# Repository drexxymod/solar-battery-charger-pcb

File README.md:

Solar Battery Charger PCB Design

This project demonstrates the design of a simple solar battery charging circuit using KiCad PCB design software.

Overview

# Solar Battery Charger PCB

## Circuit Schematic

## PCB Layout

## 3D PCB View

The circuit allows energy from a solar panel to charge a rechargeable battery while preventing reverse current flow using a protection diode.

Components

- Solar input connector
- Protection diode
- Filtering capacitor
- Battery output connector

Design Workflow

1. Circuit schematic design
2. Footprint assignment
3. PCB layout and routing
4. Board outline creation
5. 3D PCB visualization

Tools Used

- KiCad (EDA Software)
- PCB Layout Design
- Electronic Circuit Design

Preview

PCB Layout and 3D visualization created in KiCad.

Author

Hesbon O Machoka

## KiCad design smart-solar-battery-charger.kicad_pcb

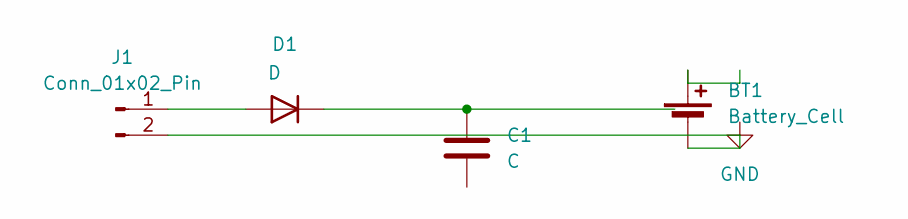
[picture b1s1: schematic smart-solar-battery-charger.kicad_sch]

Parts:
BT1: Battery_Cell; PinHeader_1x02_P2.54mm_Vertical
C1: C; CP_Radial_D6.3mm_P2.50mm
D1: D; D_DO-41_SOD81_P10.16mm_Horizontal
J1: Conn_01x02_Pin; PinHeader_1x02_P2.54mm_Vertical

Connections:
unnamed: BT1.2 (-), J1.2
unnamed: D1.2 (A), J1.1
unnamed: C1.1, D1.1 (K)

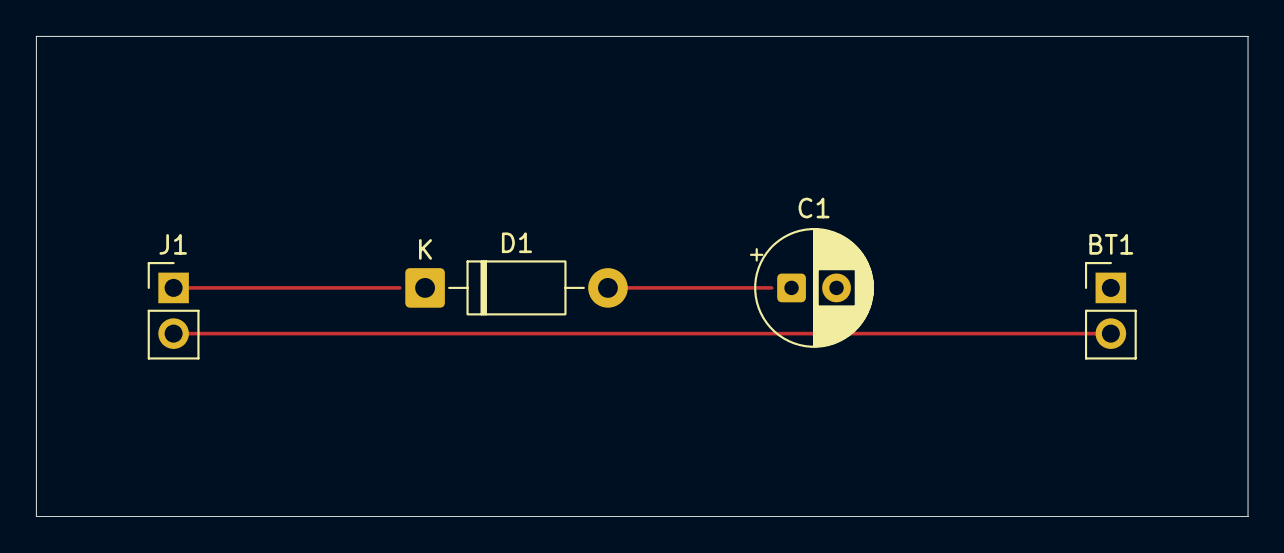
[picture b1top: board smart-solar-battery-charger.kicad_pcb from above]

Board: 2 copper layers, 67.3 x 26.7 mm, 4 parts (0 on the bottom side), 3 nets.

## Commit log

2026-03-12 Enhance README with schematic and PCB images
    Added sections for circuit schematic, PCB layout, and 3D view with images.
2026-03-12 Rename pcb-layout.ping to pcb-layout.png
